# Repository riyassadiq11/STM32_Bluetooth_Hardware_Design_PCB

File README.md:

# STM32_Bluetooth_Hardware_Design_PCB
4‑layer PCB (49 × 24 mm, 1.6 mm) using STM32WB55CEU6 for Bluetooth. Features USB‑C with ESD protection, RF + U.FL antenna, SWD debug header, and SMPS power. Includes impedance‑controlled routing, custom footprint (DLF162500LT‑5028A1), 3D STEP models, and validated with ERC/DRC checks.

# 📡 STM32WB55 Bluetooth Hardware Design (KiCad, 4‑Layer)

## 📖 Project Overview
This project is a **4‑layer PCB design** using **STM32WB55CEU6 microcontroller** for Bluetooth communication.  
It integrates USB‑C interface, RF with U.FL antenna connector, SWD debug header, and regulated 3.3V supply.  
Custom footprints and 3D models were created to ensure accurate visualization and manufacturing readiness.

---

## 📐 PCB Specifications
- **Board size:** 49 mm × 24 mm  
- **Thickness:** 1.6 mm  
- **Layers:** 4‑layer stackup  
- **Copper Pour:**  
  - **Layer 1 (Front):** Signal layer  
  - **Layer 2 (In1):** GND plane  
  - **Layer 3 (In2):** GND plane  
  - **Layer 4 (Bottom):** Power plane  
- **Impedance Control:**  
  - 50 Ω ±10% single‑ended microstrip (trace width 0.19 mm)  
  - 90 Ω ±10% differential microstrip (trace width 0.22 mm, spacing 0.15 mm)  

---

## 🔌 Schematic Explanation

### Power Supply & SMPS
- **MIC5365‑3.3 LDO regulator** converts USB 5V to 3.3V.  
- Multiple **decoupling capacitors (100nF)** placed near VDD pins.  
- **SMPS pins (VLXSMPS, SMPSLX, SMPSFB, VFBSMPS)** connected with inductors/capacitors for internal buck converter.  
- Provides efficient power delivery for RF and digital domains.
- This reduces power consumption compared to pure LDO mode.

**Working:**  
STM32WB55 uses an internal buck converter. VLXSMPS pin drives the inductor, SMPSFB senses feedback, and VFBSMPS stabilizes output.This lowers current draw and heat, especially important for battery‑powered designs.

---

### ESD Protection
- **USBLC6‑2SC6 diode array** protects USB D+ and D‑ lines.  
- Ensures compliance with USB 2.0 signal integrity while clamping high‑voltage spikes
- Prevents damage from static discharge when plugging/unplugging USB‑C.  

---

### SWD Debug Connection
- **SWD_CLK (PA14)** → Debug clock.  
- **SWD_DIO (PA13)** → Bidirectional data line.  
- **SWO (PB3)** → Trace output.  
- **NRST** → Reset line.  
- Connected via **Tag‑Connect header** for programming/debugging. 

---

### RF
- RF output routed through **matching network (L3, capacitors)**. - **DLF162500LT low‑pass filter** ensures clean 2.4–2.5 GHz band. - **U.FL coaxial connector** for external antenna.  
- Ground stitching vias improve impedance control and reduce noise.

**Working:**  
MCU generates Bluetooth RF signal → passes through matching network → filtered → sent to antenna. Impedance control (50 Ω single‑ended) ensures maximum power transfer and minimal reflection.

---

### USB‑C Interface
- USB‑C connector with **CC1/CC2 resistors** for orientation detection.  
- D+ / D‑ routed with **90 Ω differential impedance**.  
- Protected by ESD diodes.  
- VBUS feeds the LDO regulator.

---

### Peripherals
- **UART header** for communication/debugging.  
- **LED with resistor** for status indication.  
- **Push button** for Boot0/reset.  
- **Crystals:**  
  - HSE (32 MHz) → system clock.  
  - LSE (32.768 kHz) → RTC.  

---

## ✅ Design Validation
- **ERC check:** Successfully completed for schematic (no electrical rule errors).  
- **DRC check:** Successfully completed for PCB layout (no design rule violations).  

---

## ⚙️ How It Works
1. USB‑C provides 5V → LDO converts to 3.3V → SMPS stabilizes supply.  
2. MCU runs with external crystals for accurate timing.  
3. SWD header allows firmware flashing and debugging.  
4. Bluetooth RF routed through matching network + LPF → antenna.  
5. USB‑C handles data, UART header provides serial debug.  
6. ESD diodes protect USB lines, ground stitching reduces noise.  
7. LED shows status, push button controls Boot0/reset.  

---

## 🛠️ Skill Highlights
- KiCad schematic capture & 4‑layer PCB design  
- Custom footprint creation (DLF162500LT‑5028A1)  
- 3D STEP model integration (MCU, filter, crystal)  
- Impedance‑controlled routing (USB & RF)  
- SWD debug integration  
- USB‑C interface with ESD protection  
- RF matching & antenna connector design  
- ERC & DRC validation for schematic and PCB  
- Copper pour strategy (3 GND planes + 1 power plane)  
- Gerber/BOM/pick‑and‑place generation  
- Ground stitching & copper pour techniques

## Key Learnings:
- MCU & Debugging: Gained detailed knowledge of STM32WB55 pin functions, SWD interface, and MCU working principles.
- RF Engineering: Learned antenna integration, RF matching networks, and impedance‑controlled routing for Bluetooth signals.
- USB Integration: Implemented USB‑C interface with differential pair matching, controlled impedance, and ESD protection.
- Impedance Control: Calculated and applied trace width/spacing for 50 Ω single‑ended and 90 Ω differential pairs.
- PCB Stack‑Up: Understood layer stackup, core and prepreg materials (e.g., 2126), and their role in signal integrity.
- Manufacturing Readiness: Applied mounting holes, fiducial markers, and copper pour strategy (3 GND planes + 1 power plane).
- Routing Techniques: Learned via diameter selection, trace width/spacing rules, and applying specific constraints for USB and RF connections.
- Design Validation: Performed ERC and DRC checks to ensure error‑free schematic and PCB layout.

## 🖼️ Schematic

The schematic illustrates the complete STM32WB55CEU6 Bluetooth hardware design, including power supply (LDO + SMPS), USB‑C interface with ESD protection, SWD debug header, RF front‑end with matching network and U.FL antenna connector, and peripheral components (UART, LED, crystals, push button).  

/STM32WB55CEU6_Schematic.png)

## 🖼️ PCB Layout – Top Layer

The top layer layout shows the placement of STM32WB55CEU6, USB‑C connector, RF front‑end, SWD header, and supporting components.  
Silkscreen markings highlight pin labels and orientation for assembly.  
Copper pour on this layer is dedicated to the **GND plane**, ensuring stable return paths and reduced EMI.  

/Top_Layer_PCB.jpg)

## 🖼️ PCB Layout – Bottom Layer

The bottom layer layout highlights the routing of power planes and supporting traces.  
This layer is dedicated to the **power plane**, ensuring stable distribution of 3.3V and other supply rails across the board.  
It complements the three GND planes (Front, In1, In2) by providing a clean separation of power and ground, improving signal integrity and reducing noise.  

/Bottom_Layer_PCB.jpg)

## 🖼️ 3D Views

The 3D views provide a realistic visualization of the PCB assembly.  
They include custom **STEP models** for the STM32WB55CEU6 microcontroller, the DLF162500LT‑5028A1 RF filter, and the 32.768 kHz crystal.  
These models ensure accurate mechanical alignment, proper component clearance, and a professional preview of the final board.  

/Top_View_3D.png)  
/Bottom_View_3D.png)

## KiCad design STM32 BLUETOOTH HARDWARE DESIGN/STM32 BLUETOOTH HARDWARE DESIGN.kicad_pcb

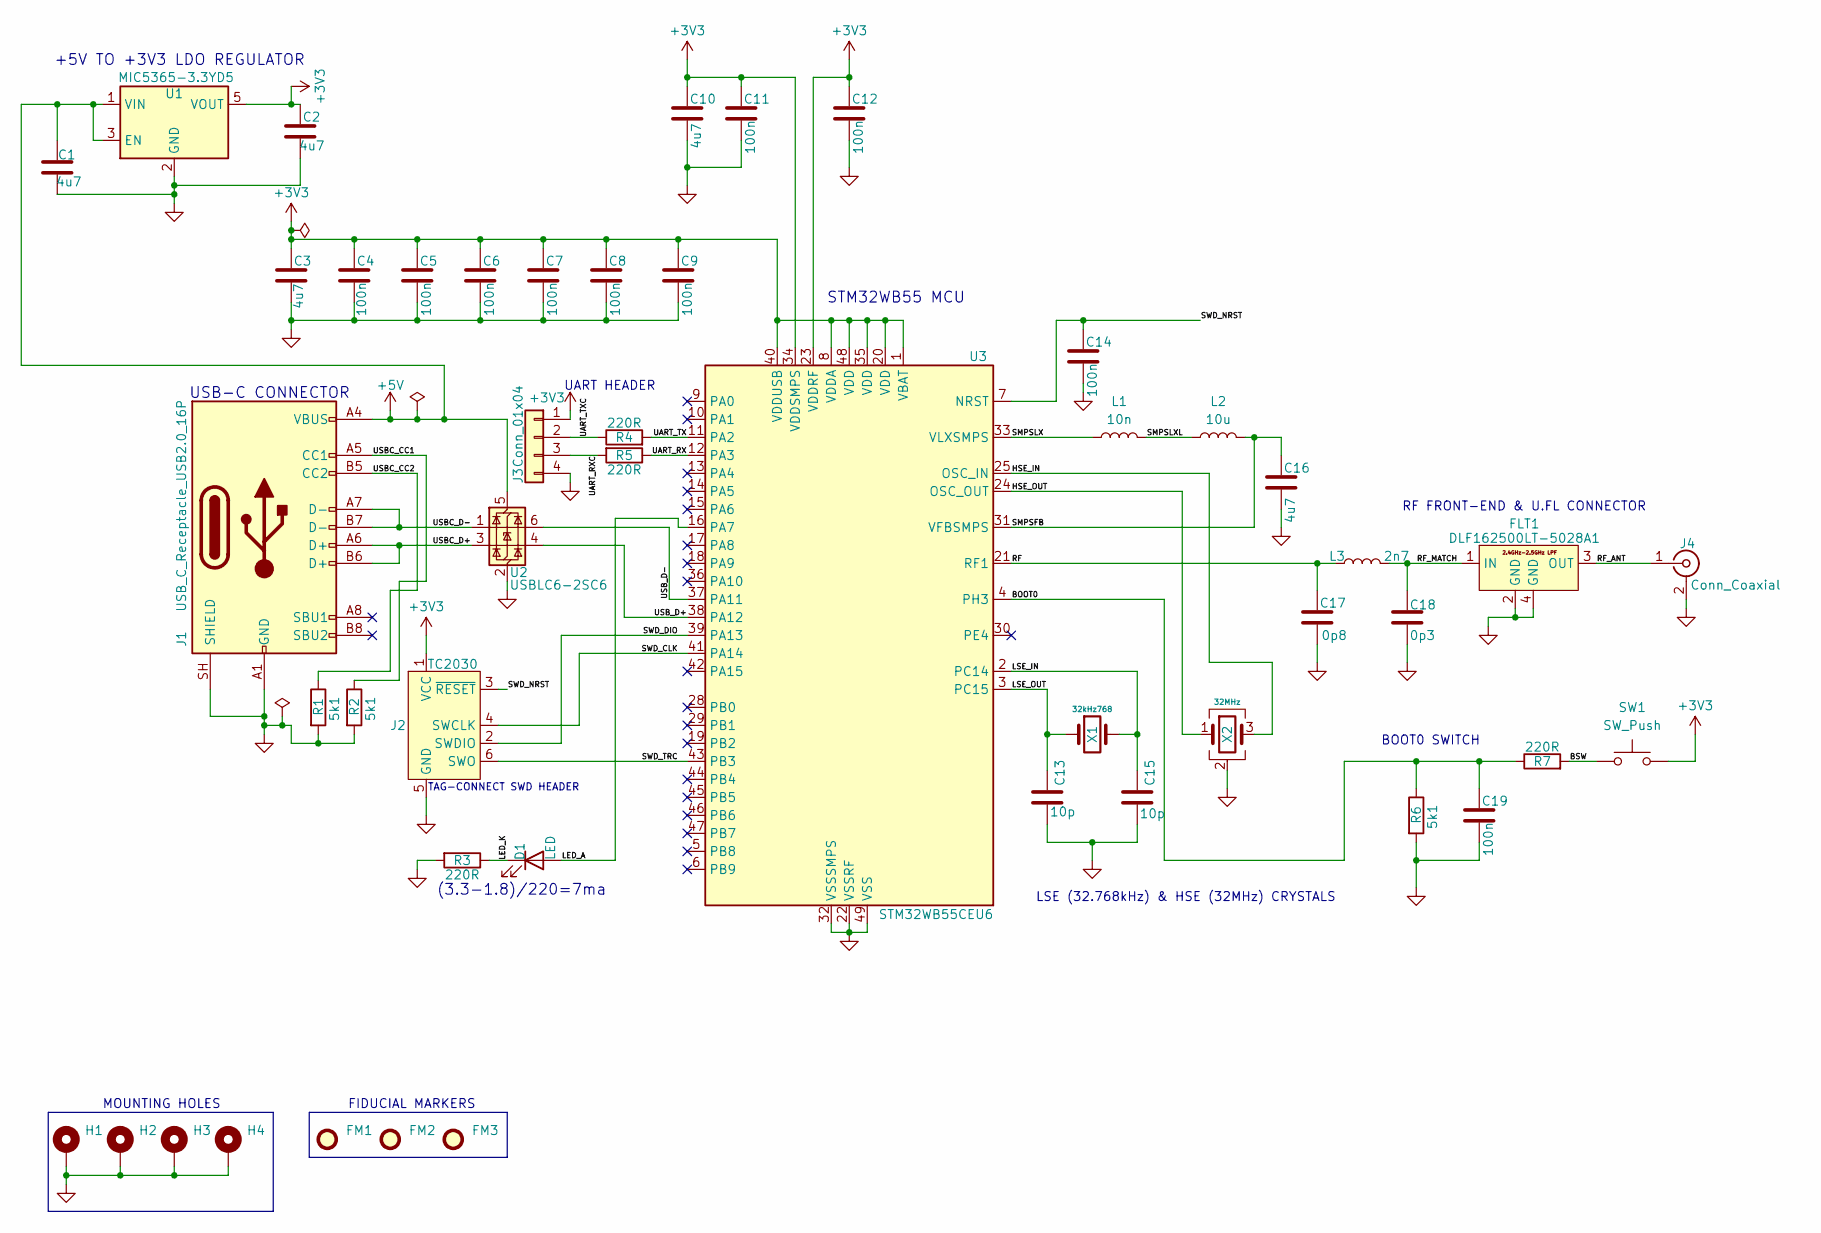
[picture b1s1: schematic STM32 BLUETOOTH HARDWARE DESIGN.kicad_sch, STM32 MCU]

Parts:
C1, C2, C3, C10, C16: 4u7; C_0603_1608Metric; Manufatcurer Part Number 0603YD475MAT2A
C4, C5, C6, C7, C8, C9, C11, C12, C14, C19: 100n; C_0402_1005Metric; Manufatcurer Part Number 04023C104KAT2A
C13, C15: 10p; C_0402_1005Metric; Manufatcurer Part Number 04025A100JAT4A
C17: 0p8; C_0402_1005Metric; Manufatcurer Part Number GRM1555C1HR80BA01D
C18: 0p3; C_0402_1005Metric; Manufatcurer Part Number GRM1555C1HR30WA01D
D1: LED; LED_0402_1005Metric; Manufatcurer Part Number 150040RS73240
FLT1: DLF162500LT-5028A1; Manufatcurer Part Number DLF162500LT-5028A1
FM1, FM2, FM3: Fiducial; Fiducial_1mm_Mask2mm
H1, H2, H3, H4: MountingHole_Pad; MountingHole_2.2mm_M2_Pad_Via
J1: USB_C_Receptacle_USB2.0_16P; USB_C_Receptacle_GCT_USB4105-xx-A_16P_TopMnt_Horizontal; Manufatcurer Part Number USB4105-GF-A
J2: TC2030; Tag-Connect_TC2030-IDC-FP_2x03_P1.27mm_Vertical
J3: Conn_01x04; Molex_PicoBlade_53048-0410_1x04_P1.25mm_Horizontal; Manufatcurer Part Number 53048-0410
J4: Conn_Coaxial; U.FL_Hirose_U.FL-R-SMT-1_Vertical; Manufatcurer Part Number U.FL-R-SMT(01)
L1: 10n; L_0402_1005Metric; Manufatcurer Part Number LQG15WZ10NJ02D
L2: 10u; L_0805_2012Metric; Manufatcurer Part Number LQM21FN100M70L
L3: 2n7; L_0402_1005Metric; Manufatcurer Part Number LQG15HS2N7S02D
R1, R2, R6: 5k1; R_0402_1005Metric; Manufatcurer Part Number RC0603FR-075K1L
R3, R4, R5, R7: 220R; R_0402_1005Metric; Manufatcurer Part Number RC0402FR-07221RL
SW1: SW_Push; SW_SPST_CK_RS282G05A3; Manufatcurer Part Number RS-282G05A3-SM RT
U1: MIC5365-3.3YD5; TSOT-23-5; Manufatcurer Part Number MIC5365-3.3YD5-TR
U2: USBLC6-2SC6; SOT-23-6; Manufatcurer Part Number USBLC6-2SC6
U3: STM32WB55CEU6; QFN-48-1EP_7x7mm_P0.5mm_EP5.6x5.6mm; Manufatcurer Part Number STM32WB55CEU6
X1: 32kHz768; Crystal_SMD_2012-2Pin_2.0x1.2mm; Manufatcurer Part Number STDMUB1-32.768K
X2: 32MHz; Crystal_SMD_2016-4Pin_2.0x1.6mm; Manufatcurer Part Number CS06465-32M

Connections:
+3V3: C2.1, C3.1, C4.1, C5.1, C6.1, C7.1, C8.1, C9.1, C10.1, C11.1, C12.1, J2.1 (VCC), J3.1, SW1.2, U1.5 (VOUT), U3.1 (VBAT), U3.8 (VDDA), U3.20 (VDD), U3.23 (VDDRF), U3.34 (VDDSMPS), U3.35 (VDD), U3.40 (VDDUSB), U3.48 (VDD)
+5V: C1.1, J1.A4 (VBUS), J1.A9 (VBUS), J1.B4 (VBUS), J1.B9 (VBUS), U1.1 (VIN), U1.3 (EN), U2.5 (VBUS)
/BOOT0: C19.1, R6.1, R7.1, U3.4 (PH3)
/BSW: R7.2, SW1.1
/HSE_IN: U3.25 (OSC_IN), X2.3
/HSE_OUT: U3.24 (OSC_OUT), X2.1
/LED_A: D1.2 (A), U3.16 (PA7)
/LED_K: D1.1 (K), R3.1
/LSE_IN: C15.1, U3.2 (PC14), X1.2
/LSE_OUT: C13.1, U3.3 (PC15), X1.1
/RF: C17.1, L3.1, U3.21 (RF1)
/RF_ANT: FLT1.3 (OUT), J4.1 (In)
/RF_MATCH: C18.1, FLT1.1 (IN), L3.2
/SMPSFB: C16.1, L2.2, U3.31 (VFBSMPS)
/SMPSLX: L1.1, U3.33 (VLXSMPS)
/SMPSLXL: L1.2, L2.1
/SWD_CLK: J2.4 (SWCLK), U3.41 (PA14)
/SWD_DIO: J2.2 (SWDIO), U3.39 (PA13)
/SWD_NRST: C14.1, J2.3 (~RESET), U3.7 (NRST)
/SWD_TRC: J2.6 (SWO), U3.43 (PB3)
/UART_RX: R5.1, U3.12 (PA3)
/UART_RXC: J3.3, R5.2
/UART_TX: R4.2, U3.11 (PA2)
/UART_TXC: J3.2, R4.1
/USBC_CC1: J1.A5 (CC1), R2.1
/USBC_CC2: J1.B5 (CC2), R1.1
/USBC_D+: J1.A6 (D+), J1.B6 (D+), U2.3 (I/O2)
/USBC_D-: J1.A7 (D-), J1.B7 (D-), U2.1 (I/O1)
/USB_D+: U2.4 (I/O2), U3.38 (PA12)
/USB_D-: U2.6 (I/O1), U3.37 (PA11)
GND: C1.2, C2.2, C3.2, C4.2, C5.2, C6.2, C7.2, C8.2, C9.2, C10.2, C11.2, C12.2, C13.2, C14.2, C15.2, C16.2, C17.2, C18.2, C19.2, FLT1.2 (GND), FLT1.4 (GND), H1.1 (1_1), H2.1 (1_1), H3.1 (1_1), H4.1 (1_1), J1.A1 (GND), J1.A12 (GND), J1.B1 (GND), J1.B12 (GND), J1.SH (SHIELD), J2.5 (GND), J3.4, J4.2 (Ext), R1.2, R2.2, R3.2, R6.2, U1.2 (GND), U2.2 (GND), U3.22 (VSSRF), U3.32 (VSSSMPS), U3.49 (VSS), X2.2 (G), X2.4 (G)

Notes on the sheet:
STM32WB55 MCU
LSE (32.768kHz) & HSE (32MHz) CRYSTALS
BOOT0 SWITCH
(3.3-1.8)/220=7ma
FIDUCIAL MARKERS
UART HEADER
RF FRONT-END & U.FL CONNECTOR
MOUNTING HOLES
USB-C CONNECTOR
+5V TO +3V3 LDO REGULATOR
TAG-CONNECT SWD HEADER

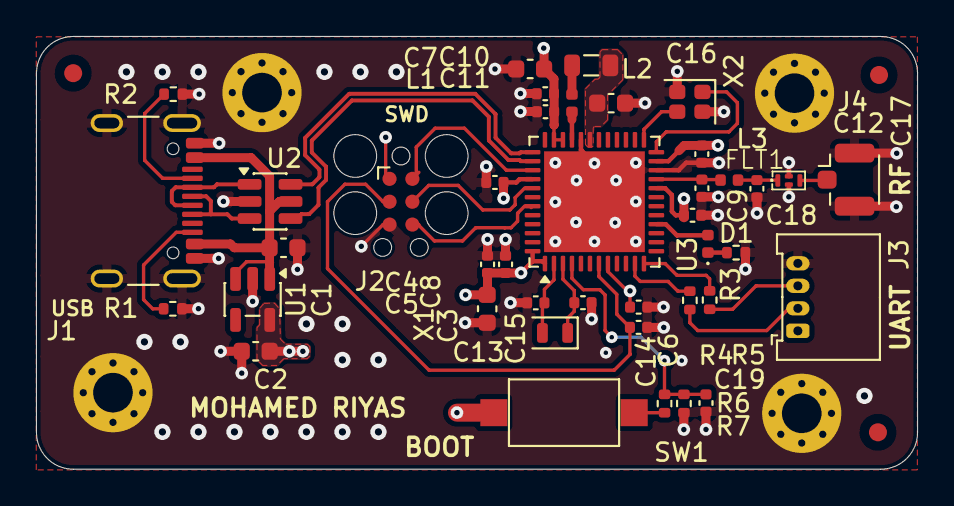
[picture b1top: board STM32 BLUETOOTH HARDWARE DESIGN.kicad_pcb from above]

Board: 4 copper layers, 49.0 x 24.0 mm, 48 parts (0 on the bottom side), 31 nets.

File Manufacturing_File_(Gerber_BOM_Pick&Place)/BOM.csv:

"Reference","Qty","Value","Footprint","Datasheet","Manufacturer","Manufatcurer Part Number","Distributer Link"
"C1,C2,C3,C10,C16","5","4u7","Capacitor_SMD:C_0603_1608Metric","","KYOCERA AVX","0603YD475MAT2A","https://www.mouser.in/en/c/?q=0603YD475MAT2A"
"C4,C5,C6,C7,C8,C9,C11,C12,C14,C19","10","100n","Capacitor_SMD:C_0402_1005Metric","","KYOCERA AVX","04023C104KAT2A","https://www.mouser.in/en/c/?q=04023C104KAT2A"
"C13,C15","2","10p","Capacitor_SMD:C_0402_1005Metric","","KYOCERA AVX","04025A100JAT4A","https://www.mouser.in/en/c/?q=04025A100JAT4A"
"C17","1","0p8","Capacitor_SMD:C_0402_1005Metric","","Murata Electronics","GRM1555C1HR80BA01D","https://www.mouser.in/en/c/?q=GRM1555C1HR80BA01D"
"C18","1","0p3","Capacitor_SMD:C_0402_1005Metric","","Murata Electronics","GRM1555C1HR30WA01D","https://www.mouser.in/en/ProductDetail/Murata-Electronics/GR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"
"D1","1","LED","LED_SMD:LED_0402_1005Metric","","Wurth Elektronik","150040RS73240","https://www.mouser.in/en/ProductDetail/Wurth-Elektronik/1500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"
"FLT1","1","DLF162500LT-5028A1","STM32 BLUETOOTH HARDWARE DESIGN_PCBFootprints:DLF162500LT-5028A1","","TDK","DLF162500LT-5028A1","https://www.mouser.in/en/ProductDetail/TDK/DLF162500LT-5028A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"
"J3","1","Conn_01x04","Connector_Molex:Molex_PicoBlade_53048-0410_1x04_P1.25mm_Horizontal","","Molex","53048-0410","https://www.mouser.in/en/ProductDetail/Molex/53048-0410?qs=3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"
"J4","1","Conn_Coaxial","Connector_Coaxial:U.FL_Hirose_U.FL-R-SMT-1_Vertical","","Hirose Connector","U.FL-R-SMT(01)","https://www.mouser.in/en/c/?q=U.FL-R-SMT%2801%29"
"L1","1","10n","Inductor_SMD:L_0402_1005Metric","","Murata Electronics","LQG15WZ10NJ02D","https://www.mouser.in/en/ProductDetail/Murata-Electronics/LQ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"
"L2","1","10u","Inductor_SMD:L_0805_2012Metric","","Murata Electronics","LQM21FN100M70L","https://www.mouser.in/en/ProductDetail/Murata-Electronics/LQ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"
"L3","1","2n7","Inductor_SMD:L_0402_1005Metric","","Murata Electronics","LQG15HS2N7S02D","https://www.mouser.in/en/ProductDetail/Murata-Electronics/LQ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"
"R1,R2,R6","3","5k1","Resistor_SMD:R_0402_1005Metric","","YAGEO","RC0603FR-075K1L","https://www.mouser.in/en/c/?q=RC0603FR-075K1L"
"R3,R4,R5,R7","4","220R","Resistor_SMD:R_0402_1005Metric","","YAGEO","RC0402FR-07221RL","https://www.mouser.in/en/ProductDetail/YAGEO/RC0402FR-07221R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"
"SW1","1","SW_Push","Button_Switch_SMD:SW_SPST_CK_RS282G05A3","","C&K","RS-282G05A3-SM RT","https://www.mouser.in/en/ProductDetail/CK/RS-282G05A3-SM-RT?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"
"X1","1","32kHz768","Crystal:Crystal_SMD_2012-2Pin_2.0x1.2mm","","NDK","STDMUB1-32.768K","https://www.mouser.in/en/ProductDetail/NDK/STDMUB1-32.768K?q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"
"X2","1","32MHz","Crystal:Crystal_SMD_2016-4Pin_2.0x1.6mm","","NDK","CS06465-32M","https://www.mouser.in/en/ProductDetail/NDK/CS06465-32M?qs=Tc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"
"U1","1","MIC5365-3.3YD5","Package_TO_SOT_SMD:TSOT-23-5","https://ww1.microchip.com/downloads/aemDocuments/documents/A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","Microchip Technology","MIC5365-3.3YD5-TR","https://www.mouser.in/en/ProductDetail/Microchip-Technology/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"
"U3","1","STM32WB55CEU6","Package_DFN_QFN:QFN-48-1EP_7x7mm_P0.5mm_EP5.6x5.6mm","https://www.st.com/resource/en/datasheet/stm32wb55ce.pdf","STMicroelectronics","STM32WB55CEU6","https://www.mouser.in/en/c/?q=STM32WB55CEU6"
"U2","1","USBLC6-2SC6","Package_TO_SOT_SMD:SOT-23-6","https://www.st.com/resource/en/datasheet/usblc6-2.pdf","STMicroelectronics","USBLC6-2SC6","https://www.mouser.in/en/c/?q=USBLC6-2SC6"
"J1","1","USB_C_Receptacle_USB2.0_16P","Connector_USB:USB_C_Receptacle_GCT_USB4105-xx-A_16P_TopMnt_Horizontal","https://www.usb.org/sites/default/files/documents/usb_type-c.zip","GCT","USB4105-GF-A","https://www.mouser.in/en/c/?q=USB4105-GF-A"
